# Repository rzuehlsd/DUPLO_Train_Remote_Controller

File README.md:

# DUPLO Train Remote Controller System

**A event-driven train remote control system for LEGO DUPLO, built on ESP32, FreeRTOS, and Bluetooth Low Energy (BLE).**

Copyright (c) 2022-2025 Ralf Zühlsdorff

This project is licensed under the terms of the MIT License. See the License section below for details.

----
## Table of Contents

- [DUPLO Train Remote Controller System](#duplo-train-remote-controller-system)
  - [Table of Contents](#table-of-contents)
  - [Project Overview](#project-overview)
  - [User Interface](#user-interface)
    - [Quick Start: Connecting a DUPLO Train](#quick-start-connecting-a-duplo-train)
    - [Button \& Encoder Actions](#button--encoder-actions)
    - [Optical Feedback (Controller RGB LED)](#optical-feedback-controller-rgb-led)
    - [Implemented Sensor Callbacks](#implemented-sensor-callbacks)
    - [Auto-Sleep \& Wake-Up](#auto-sleep--wake-up)
  - [Architecture Overview](#architecture-overview)
    - [Dual-Core Strategy](#dual-core-strategy)
    - [Future Improvements](#future-improvements)
  - [System Architecture](#system-architecture)
    - [Multi-Task Processing with Bidirectional Communication](#multi-task-processing-with-bidirectional-communication)
    - [Three-Layer Architecture](#three-layer-architecture)
    - [duploHub.init() Bootstrapping Flow](#duplohubinit-bootstrapping-flow)
  - [Features](#features)
  - [Hardware Requirements](#hardware-requirements)
    - [Primary Hardware](#primary-hardware)
    - [Supported LEGO Hardware](#supported-lego-hardware)
    - [Technical Specifications](#technical-specifications)
  - [Hardware Design](#hardware-design)
  - [Software Dependencies](#software-dependencies)
    - [Platform](#platform)
    - [Libraries](#libraries)
    - [Library Versions](#library-versions)
  - [Installation](#installation)
    - [1. Environment Setup](#1-environment-setup)
    - [2. Project Build \& Upload](#2-project-build--upload)
    - [3. Hardware Setup](#3-hardware-setup)
  - [Usage](#usage)
    - [Basic Operation](#basic-operation)
    - [Expected Serial Debug Output](#expected-serial-debug-output)
  - [API Reference](#api-reference)
    - [DuploHub Class](#duplohub-class)
      - [Connection Management](#connection-management)
      - [Control Methods (Thread-Safe)](#control-methods-thread-safe)
      - [Information Methods](#information-methods)
      - [Event Callbacks](#event-callbacks)
    - [DuploHubExtended Class (Sensor Support)](#duplohubextended-class-sensor-support)
      - [Sensor Callbacks](#sensor-callbacks)
      - [Sensor Activation (Thread-Safe)](#sensor-activation-thread-safe)
      - [Example Usage](#example-usage)
    - [Available Colors](#available-colors)
    - [Motor Speed Range](#motor-speed-range)
  - [System Monitoring](#system-monitoring)
    - [Status Information](#status-information)
    - [Log Message Prefixes](#log-message-prefixes)
  - [Troubleshooting](#troubleshooting)
    - [Common Issues \& Solutions](#common-issues--solutions)
      - [Connection Problems](#connection-problems)
      - [Task Failures](#task-failures)
      - [Command Delays](#command-delays)
    - [Debug Mode](#debug-mode)
  - [Development](#development)
    - [Project Structure](#project-structure)
    - [Adding New Features](#adding-new-features)
      - [New Train Commands](#new-train-commands)
      - [New Hub Types](#new-hub-types)
    - [Code Style Guidelines](#code-style-guidelines)
  - [Contributing](#contributing)
    - [Development Process](#development-process)
    - [Testing Checklist](#testing-checklist)
  - [Links](#links)
  - [License](#license)
  - [Acknowledgments](#acknowledgments)

---

## Project Overview

This project implements a robust, multi-layered, event-driven train controller for LEGO DUPLO trains. 

The system not only covers the firmware to controll the DUPLO train but also the required hardware and the OpenSCAD files for the case of the handheld controller.

I used a Tenstar Super Mini ESP32-S3 FH4R2 controller (yes, it is totally overkill for this application) because it provides onboard functionality as a RGB LED (used for user feedback) and a charging controller for a 3.7V Lithium battery. This onboard functionality reduced the required external components for the handheld controller to only 6 SMD switches, a rotary encoder and a few SMD resistors plus 1 capacitor.

The firmware builds on top of the open-source [Legoino](https://github.com/corneliusmunz/legoino) library created by Cornelius Munz, reusing its Powered Up protocol support while adding a hardened hardware abstraction tailored to ESP32 dual-core devices. Using both cores to implement the app signifficantly increased the overall reliability.

Key pillars of the solution include:

- **ESP32 dual-core architecture** (FreeRTOS): BLE communication runs independently from application logic for deterministic responsiveness.
- **Legoino-powered protocol stack**: Proven LEGO Powered Up discovery, device activation, and message parsing.
- **Thread-safe command and sensor queues**: Bidirectional, non-blocking communication between BLE and main application tasks.
- **Automatic connection management**: Self-healing BLE connections with exponential backoff recovery.
- **Enhanced logging and monitoring**: Real-time status, error, and performance reporting.
- **Deep Sleep and Wakeup**: In case no user interactions have been detected for more than 5 minutes the device goes to sleep and can be waked up by pressing the encoder button.

The high-level structure is summarised below; a deeper dive is available in [ARCHITECTURE.md](ARCHITECTURE.md).

## User Interface

THe handheld DUPLO train controller has 6 switches and a rotary encoder to send BLE commands to the DUPLO train hub. User feedback is provided through the onboard RGB LED of the ESP32-S3 controller.

### Quick Start: Connecting a DUPLO Train
- Power on the controller (ESP32) and the DUPLO Train Hub. 
- The DUPLO train will show a **white** blinking front light.
- The RGB LED of the controller turns to **yellow**.
- The controller immediately begins scanning for an active duplo train.
- Once internal initializatioon of the controller is completed the RBB LED turns to **green**. 
- If connected the DUPLO train will show a solid **blue** front light.
- After DUPLO train has connected, the controller’s RGB status LED turns to *blue** and blinks 3 times to confirm link.
- If no hub is found, the status LED pulses **orange** every few seconds to prompt you to power cycle or move the train closer.

### Button & Encoder Actions
- **Rotary encoder (turn):** Proportionally ramps the train motor between full reverse, neutral, and full forward with a tactile centre detent to simplify stops.
- **Rotary encoder (press):** Wakes the controller from deep sleep.
- **Record button:** Starts or stops capture of the current driving session, including speed, light, and sound changes for later replay.
- **Play button:** Replays the most recently recorded session, mirroring the captured timing for motor, LED, and audio cues. Press again to stop replay.
- **Stop button:** Issues an immediate emergency stop, cutting motor power and triggering the associated brake feedback sequence. To start normal operation the stop button **HAS TO BE PRESSED AGAIN**!
- **Light button:** Cycles through the preset DUPLO hub LED colours so the train can be themed without using a screen or app.
- **Sound button:** Steps through the curated horn, brake, and station audio effects for interactive play.
- **Water button:** Runs the refill routine, pausing the train, playing the refill sound, and resuming at the previous throttle setting.

### Optical Feedback (Controller RGB LED)
- **Blue (pulsing 5 times):** Connection to a DUPLO hub establish and ready for commands.
- **Red (slow blinking):** Recording action sequence.
- **Yellow (slow blinking):** Replaying action sequence.
- **Red (steady):** Emergency stop engaged. Goes off if button is engaged again
- **Red (fast pulses 5 times):** Signals low voltage of DUPLO train battery every 300 seconds

### Implemented Sensor Callbacks

The controller provides callback implementations for speed, voltage and color sensor events. While the speed sensor is currently not used, the voltage sensor gives warning feedback, if battery voltage of DUPLO Train drops below 5V.

The color sensor is used to detect the color bricks provided with the DUPLO train set to trigger preprogrammed actions. The detection of the correct colors is very tricky as it depends on the reflection of the color bricks. So expect some wrong colors to be detected. As we overwrite the preprogrammed actions here is a short description of the implemented actions:

- **RED** triggers a stop of the train with brake sound and red headlights
- **YELLOW** triggers departure of the train with yellow blinking headlights and horn sound
- **BLUE** triggers water refill action with blinking blue headlight, stop of train, water refill sound and departure of train with last defined speed

Currently all other colored bricks just set the headlight to the respective color.

### Auto-Sleep & Wake-Up
- After **5 minutes** without button presses or encoder turns, the controller enters deep sleep to save power; the status LED fades out to indicate standby.
- To reactivate, press the rotary encoder once to start initialization and connection cycle again

---
## Architecture Overview

The firmware is organised into three cooperating layers:

1. **Application Layer (`TrainController`)** – orchestrates user input, status LED feedback, replay/record logic, and system health checks.
2. **Hardware Abstraction Layer (`DuploHub`)** – maintains thread-safe command/response queues, sensors, and lifecycle management for the BLE task.
3. **Protocol Layer (`myLegoHub`/Legoino)** – bridges to the LEGO Powered Up protocol, handling device discovery and low-level message encoding.

These layers communicate exclusively through FreeRTOS queues and callbacks, which allows the BLE task and user interface to stay decoupled. The full architectural description, sequence diagrams, and performance considerations are documented in [ARCHITECTURE.md](ARCHITECTURE.md).

### Dual-Core Strategy

The ESP32’s two cores are used deliberately to isolate time-critical communication from user-driven workloads:

- **Core 0** is dedicated to the BLE stack (NimBLE) and the `DuploHub` task, guaranteeing consistent connection upkeep and sensor polling under tight timing constraints.
- **Core 1** runs the Arduino loop (`TrainController`), handling rotary encoder updates, button ladders, response queue processing, and visual/audible feedback without blocking the BLE stack.

This separation keeps latency predictable—even when the UI is busy—and prevents sensor interrupts or sound/LED routines from starving the communication pipeline.

### Future Improvements

- Function to pair with train (store ID and use when connecting)

---
## System Architecture

### Multi-Task Processing with Bidirectional Communication

```mermaid
graph LR
   MainTask["<b>Core 1 – Main Task</b><br/>• Application logic<br/>• User interface<br/>• Status display<br/>• Demo logic<br/>• Sensor processing<br/>• Event callbacks"]

   BleTask["<b>Core 0 – BLE Task</b><br/>• BLE operations<br/>• Hub connection<br/>• Motor commands<br/>• LED control<br/>• Sensor setup<br/>• Data parsing"]

   MainTask --> |CommandQueue| BleTask

   BleTask --> |SensorQueue| MainTask

   classDef queueStyle fill:#f2f2f2,stroke:#333,stroke-width:1px
   class CommandQueue,SensorQueue queueStyle
```

### Three-Layer Architecture

```mermaid
graph LR
   Layer1["<b>Layer 1: Application Layer</b><br/>• Train demo sequence &amp; state management<br/>• User interface &amp; status monitoring<br/>• High-level control logic<br/>• Connection event handling<br/>• Sensor data processing &amp; callbacks"]

   Layer2["<b>Layer 2: Hardware Abstraction</b><br/>• Thread-safe command queue<br/>• Bidirectional FreeRTOS queues<br/>• Multi-task management (dual-core ESP32)<br/>• Connection state management<br/>• Automatic recovery &amp; error handling<br/>• Sensor routing &amp; callback management"]

   Layer3["<b>Layer 3: Protocol Layer</b><br/>• LEGO Powered Up protocol<br/>• Bluetooth LE communication<br/>• Device discovery &amp; connection<br/>• Motor &amp; LED control commands<br/>• Sensor data parsing &amp; callbacks"]

   Layer1 -->|Clean API + sensor callbacks| Layer2
   Layer2 -->|Protocol interface + sensor integration| Layer3
```

### duploHub.init() Bootstrapping Flow

The following sequence diagram visualizes how the application brings up the BLE infrastructure when `duploHub.init()` is called from `TrainController::setup()`.

```mermaid
sequenceDiagram
   participant TC as TrainController::setup
   participant DH as DuploHub
   participant RTOS as FreeRTOS Scheduler
   participant BLE as BLE Task (Core 0)
   participant Lpf2 as Lpf2Hub

   TC->>DH: init()
   activate DH
   DH->>DH: initFreeRTOS()
   DH->>RTOS: xTaskCreatePinnedToCore(bleTaskWrapper)
   RTOS-->>DH: Task handle
   deactivate DH
   DH-->>TC: return

   RTOS->>BLE: schedule bleTaskWrapper(this)
   activate BLE
   BLE->>DH: bleTaskFunction()
   loop continuous loop
      BLE->>DH: updateBLE()
      alt Hub disconnected
         DH->>Lpf2: hub.init()
      else Hub connecting
         DH->>Lpf2: connectHub()
      end
      opt Connection state change
         DH-->>TC: onConnectedCallback()/onDisconnectedCallback()
      end
      BLE->>DH: processCommandQueue()
      DH->>Lpf2: Execute queued command
      BLE->>BLE: vTaskDelay(50 ms)
   end
```

---

## Features

- **Multi-Task BLE Management**: BLE operations run on a dedicated core, never blocking the main application.
- **Automatic Connection & Recovery**: Discovers, connects, and reconnects to DUPLO train hubs automatically.
- **Thread-Safe Commands**: Queue-based command system prevents race conditions.
- **Real-Time Control**: Low-latency motor speed and LED color control driven by rotary encoder input.
- **Sensor Integration**: Color, speed, and voltage sensors with callback support and queue isolation.
- **Color Stability Filtering**: Timer-based debounce suppresses transient color readings before they reach the UI.
- **Command Recording & Replay**: Capture user sessions and play them back with preserved timing.
- **Professional Logging**: Detailed, component-specific log messages and system status monitoring.
- **Idle Power Management**: Automatic deep sleep after configurable idle periods, resume via encoder button.
- **Resource Management**: Proper FreeRTOS object lifecycle management.
- **Input Abstraction**: ADC button ladder and rotary encoder handlers with debounced callbacks.
- **Demo Mode**: Non-blocking demo sequence with visual feedback and safety features.

---

## Hardware Requirements

### Primary Hardware

- **ESP32 Development Board ESP32-S3 Super Mini** (see link below)
    I use the Tenstar ESP32-S3 FH4R2 SuperMini which also includes cuircits to charge a 3.7V Lithium battery.
- **LEGO DUPLO Train Hub** with motor connected to Port A
- **USB Type C Cable** for programming and power

### Supported LEGO Hardware

- DUPLO Train Hub (Hub Type: `DUPLO_TRAIN_HUB`)
- DUPLO Train Motors (connected to Port A)
- Compatible with other Powered Up hubs (with minor modifications)

### Technical Specifications

- **Microcontroller**: ESP32 (dual-core, 240MHz)
- **Memory**: 520KB SRAM, 4MB Flash minimum
- **Connectivity**: Bluetooth 4.2 LE
- **Operating Voltage**: 3.3V
- **Power Consumption**: ~130mA during active BLE operation

---

## Hardware Design

The following images show the KiCAD 3d view of the controller pcb and the OpenSCAD view of the controller case. To design the controller case the MachineBlocks library from pks5 (https://github.com/pks5/machineblocks) has been used.

- A dedicated ESP32-S3 carrier board with battery management and button/encoder headers is captured in KiCad inside `hardware/DuploTrainController NG`.
- A matching printable enclosure is modelled in OpenSCAD in `hardware/Case`, which also embeds the MachineBlocks library to speed up iteration on DUPLO-sized parts.

See [hardware/Hardware.md](hardware/Hardware.md) for a detailed description of the custom controller hardware.

## Software Dependencies

### Platform
- **PlatformIO**: Development platform
- **ESP32 Arduino Framework**: Core ESP32 support
- **FreeRTOS**: Real-time operating system (included with ESP32)

### Libraries

- **Legoino**: LEGO Powered Up protocol implementation by Cornelius Munz
- **NimBLE-Arduino**: Bluetooth Low Energy stack

All other libs used are provided as source in include and src dir.

### Library Versions

```ini
[env:esp32dev]
platform = espressif32
board = esp32dev
framework = arduino
lib_deps = 
    legoino/Legoino
    h2zero/NimBLE-Arduino
```

---

## Installation

Th development of this code has been done with MS Studio Code and PlatformIO.

### 1. Environment Setup

```bash
# Install PlatformIO CLI
pip install platformio

# Clone the repository
git clone <repository-url>
cd DuploTrain
```

### 2. Project Build & Upload

```bash
# Build the project
pio run

# Upload to ESP32
pio run --target upload

# Open serial monitor
pio device monitor
```

### 3. Hardware Setup

1. Connect ESP32 to computer via USB
2. Power on your DUPLO train hub
3. Ensure motor is connected to Port A of the hub
4. Upload and run the code

---

## Usage

### Basic Operation

1. **Startup**: System automatically starts and begins scanning for DUPLO hubs
2. **Connection**: When hub is found, automatic connection is established
3. **Demo**: Once connected, the demo sequence begins automatically
4. **Monitoring**: Status information is displayed every 10 seconds

### Expected Serial Debug Output

```text
TrainController: Starting up...
DuploHub: FreeRTOS objects initialized
DuploHub: BLE task started successfully
TrainController: Ready - BLE task running, waiting for hub connection...
BLE Task: Started successfully
BLE Task: Attempting initial connection to hub...
BLE Task: Connected to HUB
TrainController: Hub connected - initializing train demo!
TrainController: Starting train demo sequence...
TrainController Status - BLE Task: Running, Hub Connected: Yes, Demo Active: Yes
```

---

## API Reference

### DuploHub Class

#### Connection Management

```cpp
void startBLETask();                    // Start background BLE task
void stopBLETask();                     // Stop background BLE task
bool isConnected();                     // Check connection status (thread-safe)
bool isConnecting();                    // Check if connecting (thread-safe)
bool isDisconnected();                  // Check if disconnected (thread-safe)
bool isBLETaskRunning();                // Check BLE task status
```

#### Control Methods (Thread-Safe)

```cpp
void setMotorSpeed(int speed);          // Set motor speed (-100 to 100)
void stopMotor();                       // Stop motor immediately
void setLedColor(Color color);          // Set hub LED color
void setHubName(const char* name);      // Set hub name
```

#### Information Methods

```cpp
std::string getHubAddress();            // Get hub BLE address
std::string getHubName();               // Get hub name
byte getMotorPort();                    // Get configured motor port
void setMotorPort(byte port);           // Set motor port
```

#### Event Callbacks

```cpp
void setOnConnectedCallback(ConnectionCallback callback);     // Hub connected event
void setOnDisconnectedCallback(ConnectionCallback callback);  // Hub disconnected event
```

### DuploHubExtended Class (Sensor Support)

#### Sensor Callbacks

```cpp
typedef void (*ColorSensorCallback)(int color, byte port);
typedef void (*DistanceSensorCallback)(int distance, byte port);
typedef void (*ButtonCallback)(ButtonState state);

void setOnColorSensorCallback(ColorSensorCallback callback);      // Color sensor events
void setOnDistanceSensorCallback(DistanceSensorCallback callback);  // Distance sensor events
void setOnButtonCallback(ButtonCallback callback);                 // Button press events
```

#### Sensor Activation (Thread-Safe)

```cpp
void activateColorSensor(byte port);      // Activate color sensor on specified port
void activateDistanceSensor(byte port);   // Activate distance sensor on specified port
void activateButton();                    // Activate hub button monitoring
```

#### Example Usage

```cpp
// Color-based speed control
void onColorDetected(int color, byte port) {
    if (color == (byte)Color::RED) {
        duploHub.stopMotor();           // Emergency stop
    } else if (color == (byte)Color::GREEN) {
        duploHub.setMotorSpeed(50);     // Fast speed
    }
    duploHub.setLedColor((Color)color); // Match LED to detected color
}

// Setup
DuploHubExtended duploHub;
duploHub.setOnColorSensorCallback(onColorDetected);
duploHub.activateColorSensor((byte)PoweredUpHubPort::B);
```

### Available Colors

```cpp
BLACK, PINK, PURPLE, BLUE, LIGHTBLUE, CYAN, GREEN, YELLOW, ORANGE, RED, WHITE
```

### Motor Speed Range

- **Range**: -100 to 100
- **Positive**: Forward direction
- **Negative**: Backward direction
- **Zero**: Stop (equivalent to `stopMotor()`)

---

## System Monitoring

- **BLE Task**: Runs on Core 0, Priority 2
- **Main Loop**: Runs on Core 1, Priority 1
- **Connection Checks**: Every 1 second
- **Command Processing**: Every 50ms
- **Status Updates**: Every 10 seconds

### Status Information

The system provides comprehensive monitoring through serial output:

```text
TrainController Status - BLE Task: Running, Hub Connected: Yes, Demo Active: Yes
```

### Log Message Prefixes

- **`TrainController:`** - Main application messages
- **`BLE Task:`** - Background BLE task messages  
- **`DuploHub:`** - Hardware abstraction layer messages
- **`ERROR:`** - Critical system errors
- **`WARNING:`** - Non-critical issues

---

## Troubleshooting

### Common Issues & Solutions

#### Connection Problems
- Ensure DUPLO hub is powered on and in pairing mode
- Check if hub is already connected to another device
- Reset hub by holding button for 10 seconds
- Move ESP32 closer to hub (within 5 meters)

#### Task Failures
- Check available heap memory: `ESP.getFreeHeap()`
- Reduce other running tasks
- Increase stack size in `startBLETask()`

#### Command Delays
- Check command queue status
- Verify BLE connection stability
- Reduce command frequency in application

### Debug Mode

Enable detailed debugging by adding to `platformio.ini`:

```ini
build_flags = -DCORE_DEBUG_LEVEL=4
monitor_filters = esp32_exception_decoder
```

---

## Development

### Project Structure

```text
DuploTrain NG/
├── hardware/
│   ├── Case/
│   │   ├── Controller.scad
│   │   ├── MachineBlocks/
│   │   └── lib/
│   ├── DuploTrainController NG/
│   │   ├── DuploTrainController NG.kicad_pcb
│   │   ├── DuploTrainController NG.kicad_sch
│   │   ├── DuploTrainController NG.kicad_pro
│   │   ├── DuploTrainController NG.kicad_prl
│   │   ├── DuploTrainController NG.kicad_pcb.zip
│   │   ├── 5 Buttons an ADC.xlsx
│   │   └── Gerber/
│   └── README.md
├── include/
│   ├── ADCButton.h
│   ├── DuploHub.h
│   ├── StatusLED.h
│   ├── SystemMemory.h
│   ├── debug.h
│   └── myLegoHub.h
├── lib/
│   ├── Legoino/
│   └── NimBLE-Arduino/
├── src/
│   ├── ADCButton.cpp
│   ├── DuploHub.cpp
│   ├── StatusLED.cpp
│   ├── SytemMemory.cpp
│   ├── TrainController.cpp
│   ├── debug.cpp
│   └── myLegoHub.cpp
├── test/
│   ├── DuploTrainTests.cpp
│   ├── DuploTrainTests.h
│   └── README.md
├── ARCHITECTURE.md
├── CHANGELOG.md
├── platformio.ini
└── README.md
```

### Adding New Features

#### New Train Commands
1. Add command type to `CommandType` enum in `DuploHub.h`
2. Add command data structure to `HubCommand` union
3. Implement thread-safe method in `DuploHub` class
4. Add processing logic to `processCommandQueue()`

#### New Hub Types
1. Modify hub type detection in BLE scanning
2. Add hub-specific command handling
3. Update motor port configurations if needed

### Code Style Guidelines
- Use clear, descriptive variable names
- Add comprehensive comments for complex logic
- Follow Arduino coding standards
- Use thread-safe practices for shared data
- Include error handling for all operations

---

## Contributing

### Development Process
1. Fork the repository
2. Create feature branch (`git checkout -b feature/new-feature`)
3. Follow code style guidelines
4. Add comprehensive comments
5. Test thoroughly on hardware
6. Submit pull request with detailed description

### Testing Checklist
- [ ] Builds without warnings
- [ ] Connects to DUPLO hub successfully
- [ ] Motor control works in both directions
- [ ] LED colors change correctly
- [ ] Reconnection works after power cycle
- [ ] No memory leaks during long operation
- [ ] Task monitoring shows healthy system

---

## Links

- [ESP32 Super Mini](https://de.aliexpress.com/item/1005010463397231.html?spm=a2g0o.productlist.main.4.54df76f7WPz7SU&aem_p4p_detail=202512080110153593710143562560003446235&algo_pvid=2100b7c8-e2b1-442a-bd2c-1100bbdba2ac&algo_exp_id=2100b7c8-e2b1-442a-bd2c-1100bbdba2ac-3&pdp_ext_f=%7B%22order%22%3A%222%22%2C%22eval%22%3A%221%22%2C%22fromPage%22%3A%22search%22%7D&pdp_npi=6%40dis%21EUR%215.49%215.49%21%21%2144.13%2144.13%21%40211b612817651850154035955e1646%2112000052495017919%21sea%21DE%216288981052%21X%211%210%21n_tag%3A-29919%3Bd%3A6804e1a2%3Bm03_new_user%3A-29895&curPageLogUid=KEHYNdqLToXo&utparam-url=scene%3Asearch%7Cquery_from%3A%7Cx_object_id%3A1005010463397231%7C_p_origin_prod%3A&search_p4p_id=202512080110153593710143562560003446235_1)
- [Lithium Battery 3.7V](https://de.aliexpress.com/item/1005004378108918.html?spm=a2g0o.detail.pcDetailTopMoreOtherSeller.5.39c7kCFakCFaZ4&gps-id=pcDetailTopMoreOtherSeller&scm=1007.14452.478275.0&scm_id=1007.14452.478275.0&scm-url=1007.14452.478275.0&pvid=03756532-275c-4ab9-bd8a-2053af674cb4&_t=gps-id:pcDetailTopMoreOtherSeller,scm-url:1007.14452.478275.0,pvid:03756532-275c-4ab9-bd8a-2053af674cb4,tpp_buckets:668%232846%238108%231977&pdp_ext_f=%7B%22order%22%3A%2247%22%2C%22eval%22%3A%221%22%2C%22sceneId%22%3A%2230050%22%2C%22fromPage%22%3A%22recommend%22%7D&pdp_npi=6%40dis%21EUR%215.68%214.09%21%21%216.46%214.65%21%4021038e6617651853991155852e878e%2112000028967861661%21rec%21DE%216288981052%21X%211%210%21n_tag%3A-29919%3Bd%3A6804e1a2%3Bm03_new_user%3A-29895&utparam-url=scene%3ApcDetailTopMoreOtherSeller%7Cquery_from%3A%7Cx_object_id%3A1005004378108918%7C_p_origin_prod%3A&search_p4p_id=202512080116391515856091447492685637_4)
- [MachineBlocks](https://github.com/pks5/machineblocks)
---

## License

MIT License

Permission is hereby granted, free of charge, to any person obtaining a copy
of this software and associated documentation files (the "Software"), to deal
in the Software without restriction, including without limitation the rights
to use, copy, modify, merge, publish, distribute, sublicense, and/or sell
copies of the Software, and to permit persons to whom the Software is
furnished to do so, subject to the following conditions:

The above copyright notice and this permission notice shall be included in all
copies or substantial portions of the Software.

THE SOFTWARE IS PROVIDED "AS IS", WITHOUT WARRANTY OF ANY KIND, EXPRESS OR
IMPLIED, INCLUDING BUT NOT LIMITED TO THE WARRANTIES OF MERCHANTABILITY,
FITNESS FOR A PARTICULAR PURPOSE AND NONINFRINGEMENT. IN NO EVENT SHALL THE
AUTHORS OR COPYRIGHT HOLDERS BE LIABLE FOR ANY CLAIM, DAMAGES OR OTHER
LIABILITY, WHETHER IN AN ACTION OF CONTRACT, TORT OR OTHERWISE, ARISING FROM,
OUT OF OR IN CONNECTION WITH THE SOFTWARE OR THE USE OR OTHER DEALINGS IN THE
SOFTWARE.

---

## Acknowledgments

- **Cornelius Munz** - Legoino library creator
- **LEGO Group** - DUPLO and Powered Up hardware
- **Espressif** - ESP32 platform
- **Arduino Community** - Framework and libraries

---

**Version:** 2.0.0  
**Last Updated:** July 2025  
**Compatibility:** ESP32, Arduino Framework, PlatformIO

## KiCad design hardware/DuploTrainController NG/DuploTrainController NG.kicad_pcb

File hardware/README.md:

# Hardware Assets

This directory now contains the complete KiCad design files for the **DuploTrainController NG** handheld controller together with the generated Gerber fabrication outputs.  The top-level structure is:

```
hardware/
├── Case/                       # Enclosure or mechanical assets (empty placeholder for now)
├── DuploTrainController NG/    # KiCad project directory
│   ├── DuploTrainController NG.kicad_pro
│   ├── DuploTrainController NG.kicad_pcb
│   ├── DuploTrainController NG.kicad_sch
│   ├── DuploTrainController NG.kicad_prl
│   ├── DuploTrainController NG.kicad_pcb.zip
│   ├── 5 Buttons an ADC.xlsx
│   ├── Gerber/                 # Fabrication outputs
│   └── fp-info-cache           # Footprint cache
└── README.md                   # This document
```

Open the project in KiCad using `DuploTrainController NG.kicad_pro`.  The spreadsheet documents the ADC ladder calculations for the push buttons.  The `Gerber/` folder contains ready-to-send manufacturing files that match the current PCB revision.

> **Note:** Large binary and generated files are intentionally stored in version control so collaborators have an exact copy of the board as fabricated.  If you regenerate outputs, please audit the diffs before committing to avoid unnecessary churn.

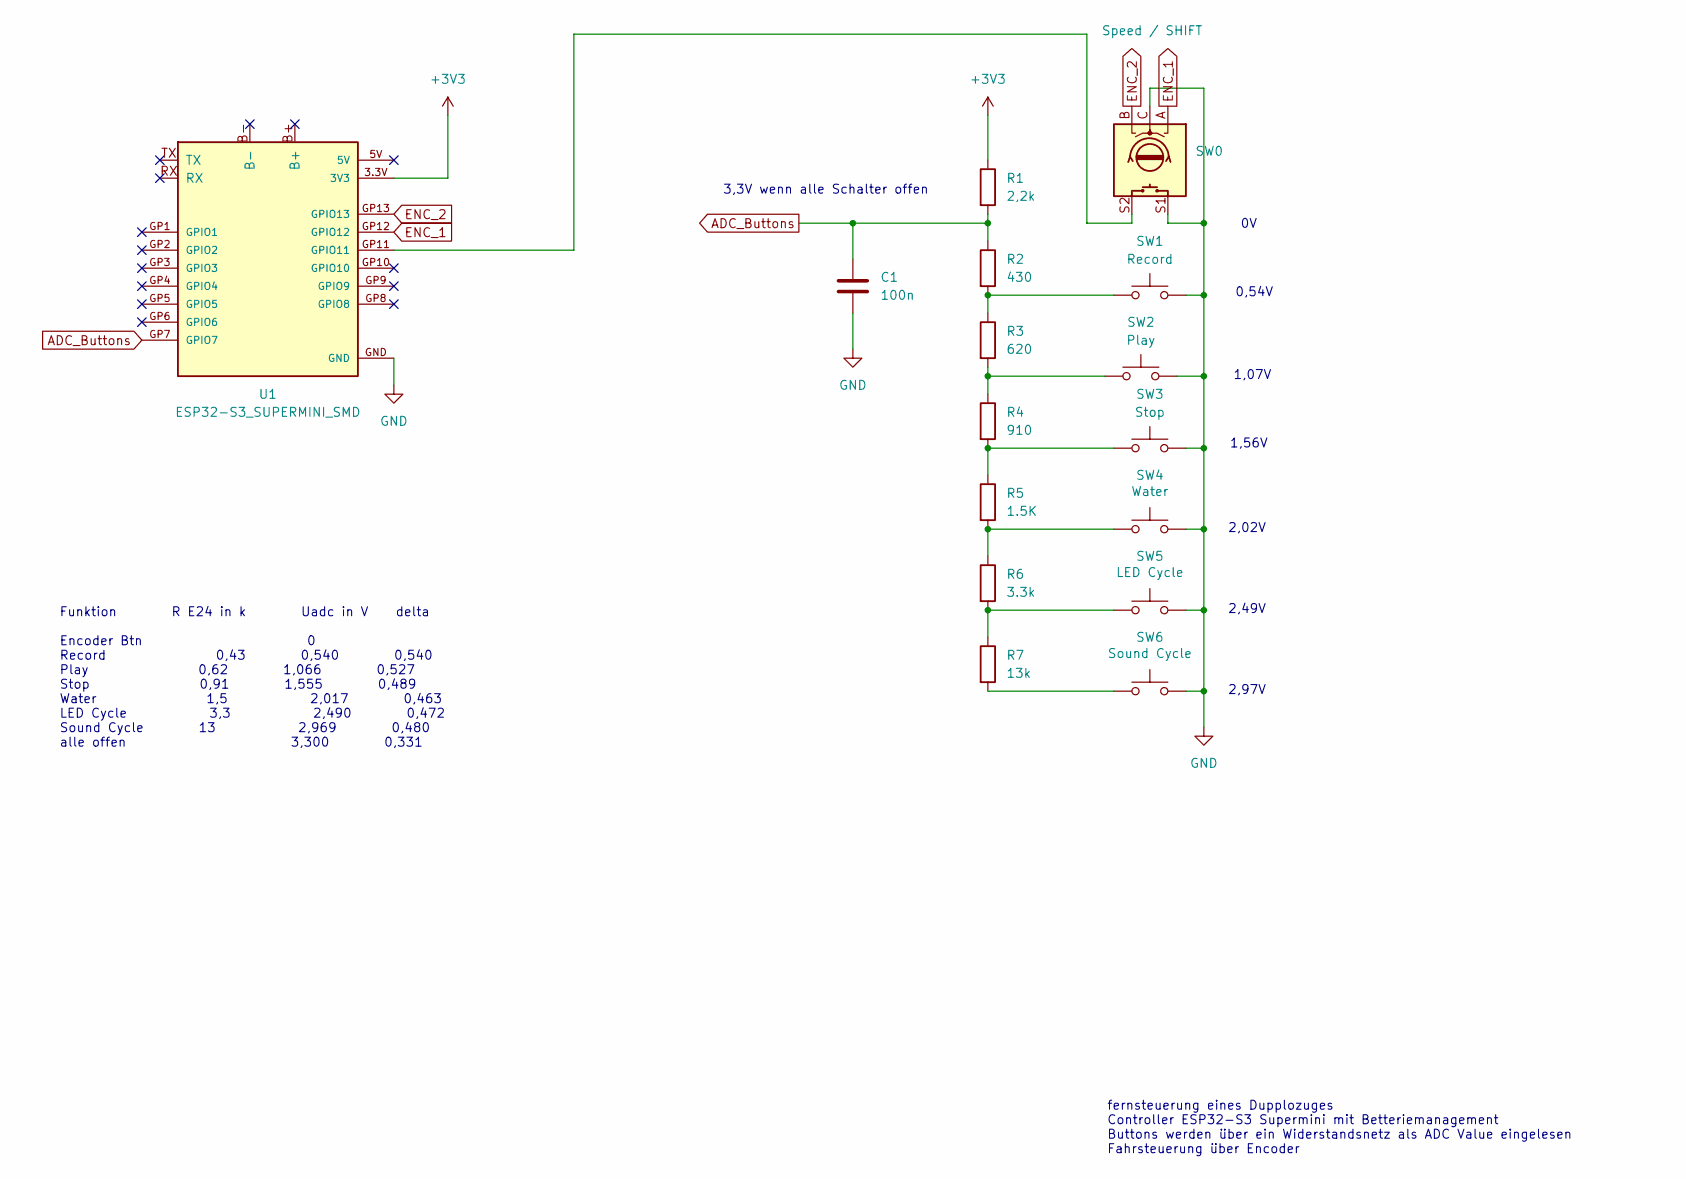
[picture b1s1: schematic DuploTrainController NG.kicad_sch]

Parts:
C1: 100n; C_Rect_L7.0mm_W2.0mm_P5.00mm
R1: 2,2k; R_0805_2012Metric_Pad1.20x1.40mm_HandSolder
R2: 430; R_0805_2012Metric_Pad1.20x1.40mm_HandSolder
R3: 620; R_0805_2012Metric_Pad1.20x1.40mm_HandSolder
R4: 910; R_0805_2012Metric_Pad1.20x1.40mm_HandSolder
R5: 1.5K; R_0805_2012Metric_Pad1.20x1.40mm_HandSolder
R6: 3.3k; R_0805_2012Metric_Pad1.20x1.40mm_HandSolder
R7: 13k; R_0805_2012Metric_Pad1.20x1.40mm_HandSolder
SW0: Speed / SHIFT; RotaryEncoder_Bourns_Vertical_PEC12R-3x17F-Sxxxx
SW1: Record; SW_SPST_Omron_B3FS-101xP
SW2: Play; SW_SPST_Omron_B3FS-101xP
SW3: Stop; SW_SPST_Omron_B3FS-101xP
SW4: Water; SW_SPST_Omron_B3FS-101xP
SW5: LED Cycle; SW_SPST_Omron_B3FS-101xP
SW6: Sound Cycle; SW_SPST_Omron_B3FS-101xP
U1: ESP32-S3_SUPERMINI_SMD; MODULE_ESP32-S3_SUPERMINI_SMD

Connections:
+3V3: R1.1, U1.3.3V (3V3)
ADC_Buttons: C1.1, R1.2, R2.1, U1.GP7 (GPIO7)
ENC_1: SW0.A, U1.GP12 (GPIO12)
ENC_2: SW0.B, U1.GP13 (GPIO13)
GND: C1.2, SW0.C, SW0.S1, SW1.2, SW2.2, SW3.2, SW4.2, SW5.2, SW6.2, U1.GND
unnamed: R2.2, R3.1, SW1.1
unnamed: R3.2, R4.1, SW2.1
unnamed: R4.2, R5.1, SW3.1
unnamed: R5.2, R6.1, SW4.1
unnamed: R6.2, R7.1, SW5.1
unnamed: R7.2, SW6.1
unnamed: SW0.S2, U1.GP11 (GPIO11)

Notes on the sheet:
2,02V
0,54V
2,49V
1,07V
fernsteuerung eines Dupplozuges Controller ESP32-S3 Supermini mit Betteriemanagement Buttons werden über ein Widerstandsnetz als ADC Value eingelesen Fahrsteuerung über Encoder
3,3V wenn alle Schalter offen
2,97V
Funktion R E24 in k Uadc in V delta Encoder Btn 0 Record 0,43 0,540 0,540 Play 0,62 1,066 0,527 Stop 0,91 1,555 0,489 Water 1,5 2,017 0,463 LED Cycle 3,3 2,490 0,472 Sound Cycle 13 2,969 0,480 alle offen 3,300 0,331
1,56V

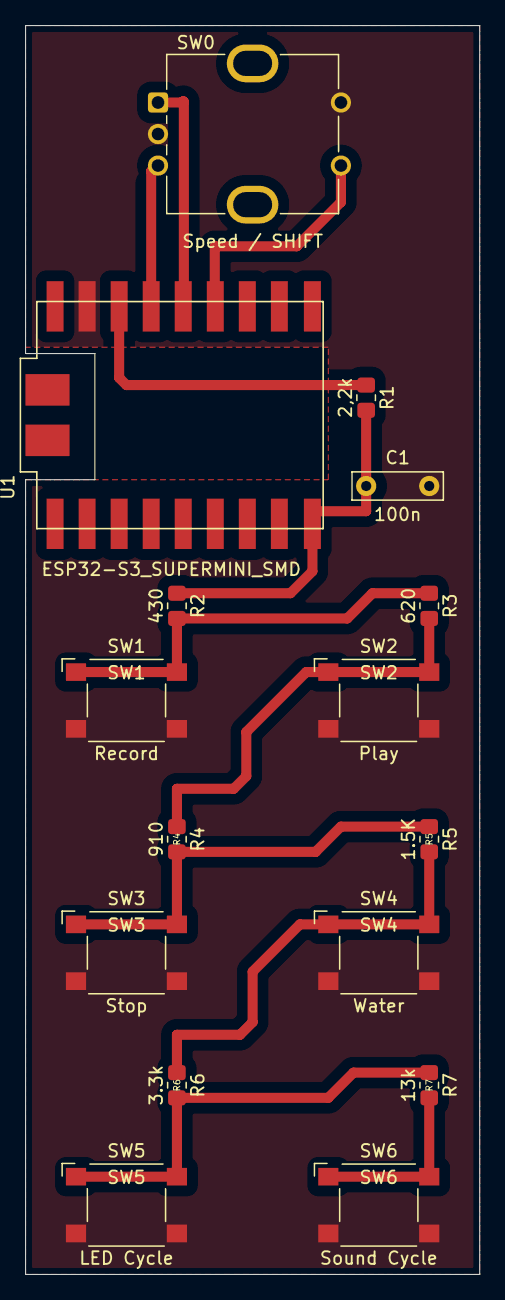
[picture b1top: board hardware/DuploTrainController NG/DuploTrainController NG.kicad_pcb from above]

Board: 2 copper layers, 36.0 x 99.0 mm, 16 parts (0 on the bottom side), 12 nets.

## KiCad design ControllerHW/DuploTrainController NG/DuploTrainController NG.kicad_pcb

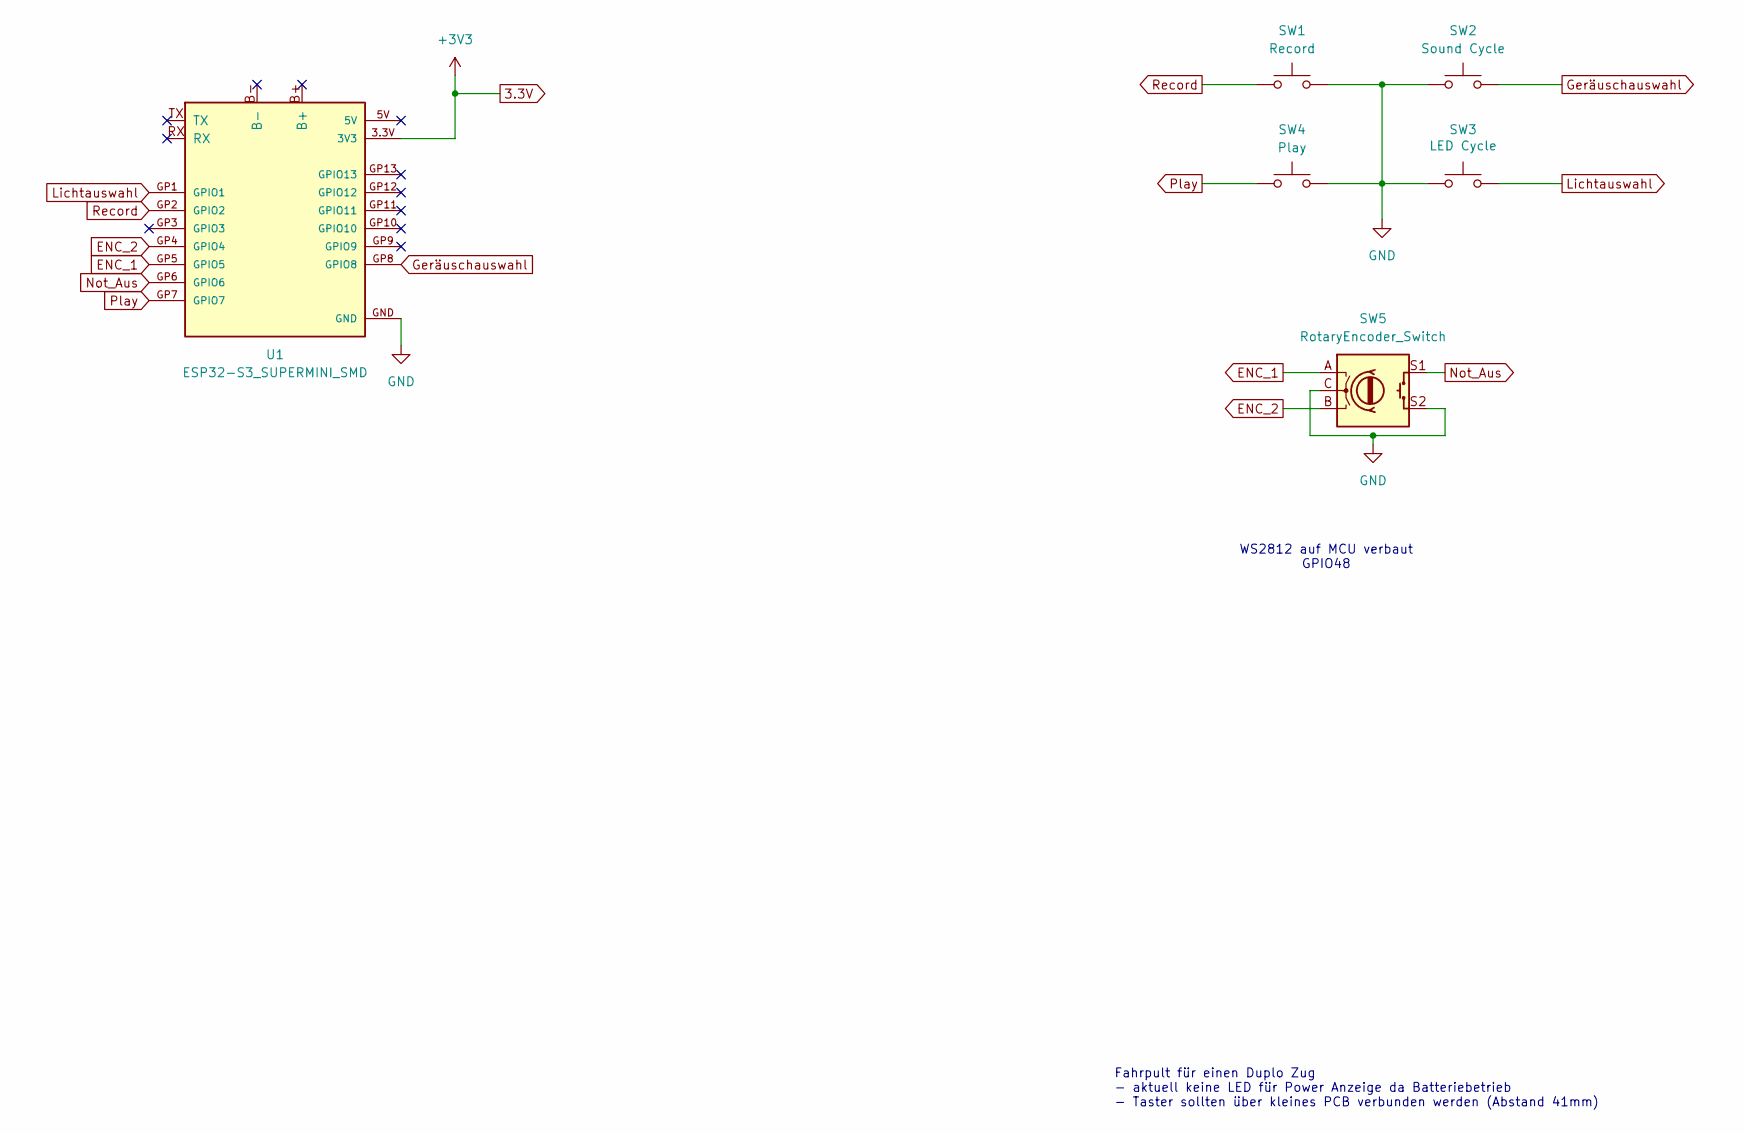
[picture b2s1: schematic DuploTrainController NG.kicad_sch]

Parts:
SW1: Record; SW_Push_1P1T_NO_CK_KSC6xxJ
SW2: Sound Cycle; SW_Push_1P1T_NO_CK_KSC6xxJ
SW3: LED Cycle; SW_Push_1P1T_NO_CK_KSC6xxJ
SW4: Play; SW_Push_1P1T_NO_CK_KSC6xxJ
SW5: RotaryEncoder_Switch; RotaryEncoder_Bourns_Vertical_PEC12R-3x17F-Sxxxx
U1: ESP32-S3_SUPERMINI_SMD; MODULE_ESP32-S3_SUPERMINI_SMD

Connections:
3.3V: U1.3.3V (3V3)
ENC_1: SW5.A, U1.GP5 (GPIO5)
ENC_2: SW5.B, U1.GP4 (GPIO4)
GND: SW1.2, SW2.1, SW3.1, SW4.2, SW5.C, SW5.S2, U1.GND
Geräuschauswahl: SW2.2, U1.GP8 (GPIO8)
Lichtauswahl: SW3.2, U1.GP1 (GPIO1)
Not_Aus: SW5.S1, U1.GP6 (GPIO6)
Play: SW4.1, U1.GP7 (GPIO7)
Record: SW1.1, U1.GP2 (GPIO2)

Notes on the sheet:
Fahrpult für einen Duplo Zug - aktuell keine LED für Power Anzeige da Batteriebetrieb - Taster sollten über kleines PCB verbunden werden (Abstand 41mm)
WS2812 auf MCU verbaut GPIO48

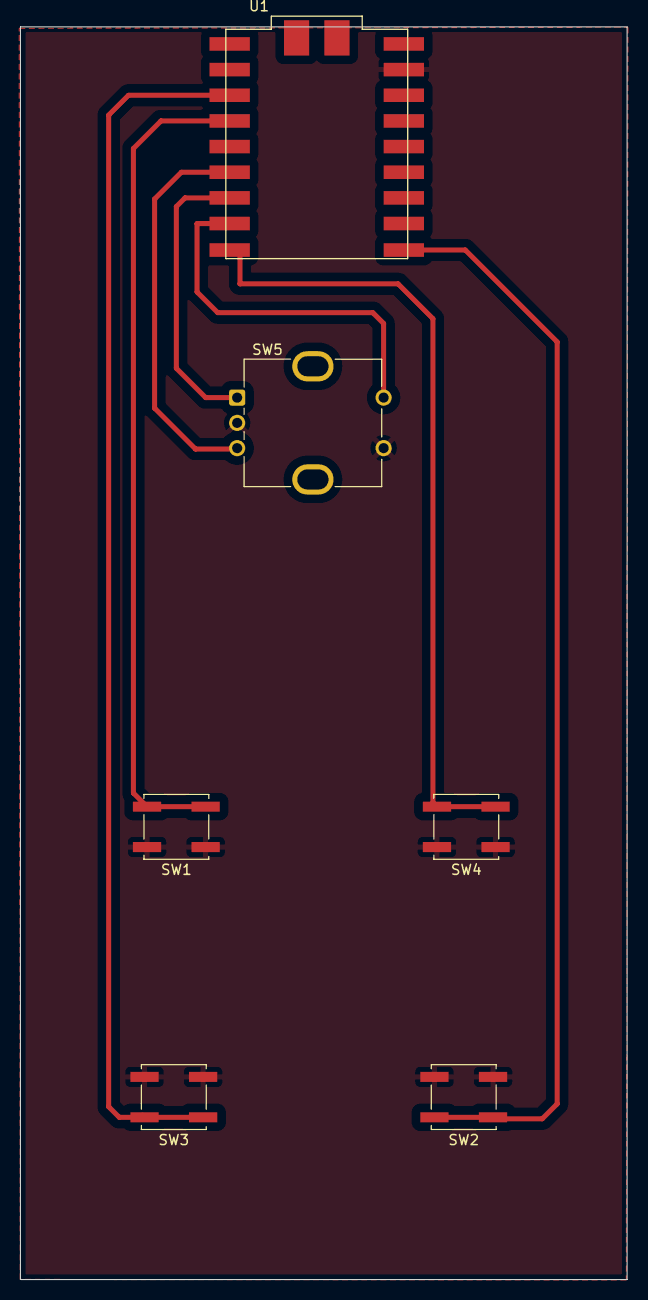
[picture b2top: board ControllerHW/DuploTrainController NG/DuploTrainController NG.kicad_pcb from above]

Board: 2 copper layers, 60.0 x 124.0 mm, 6 parts (0 on the bottom side), 8 nets.

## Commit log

2025-07-20 Initial
2025-07-20 reconnect integrated
2025-07-20 feat: Implement multi-core architecture for DUPLO Train Controller
    - Add DuploHub class with thread-safe API and FreeRTOS integration
    - Implement BLE operations on dedicated task (Core 0)
    - Add command queue system for inter-task communication
    - Rename TrainHub.cpp to TrainController.cpp for semantic clarity
    - Add automatic connection recovery with background monitoring
    - Implement mutex-based synchronization for thread safety
2025-07-20 feat: Add extended sensor support with bidirectional data processing
    - Implement DuploHubExtended class with sensor callback system
    - Add bidirectional FreeRTOS queues (commands + sensor data)
    - Create static callback wrappers for Lpf2Hub integration
    - Add TrainController_Extended.cpp with color-based speed control
    - Implement real-time sensor processing with ~75ms total latency
    - Add comprehensive sensor processing chain documentation
2025-07-21 test shell and documentation
2025-07-21 intermediate state not aligned between cpp and h files
2025-07-21 DuploHub and TrainController implemented with motor controll, color led control and sound control and succesfully implemented Fronend running on core 1 and BLE related backend task running on Core 0 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
2025-07-21 documentation updated High delay between initalization of command and execution in lego device needs further investigation
2025-07-22 playSoung function in Lpf2Hub needs an initialization per call which delays abaout 5 - 10 seconds Investigate further
2025-07-22 Timing results: - setSpedd about 5ms - setColor about 12ms
2025-07-22 testing play sound delay: - delay 5ms
2025-07-24 initiale Implementierung sensor Callback und response queue Test steht noch aus
2025-07-24 - debug log macros und functions generated - mutex print does not allways function - detection of colors with duplo base sensor seems to function, but has to be tested with different duplo color stic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
2025-07-27 intermediate version mit color und speed sensor fehler: kommandos werden nicht übertragen an device
2025-07-27 Sound, LED, Motor, Speed und Color callback ok Speed cb liefert Werte zwischen -255 und + 255, muss ggf in DuploHub angeüpasst werden auf Wertebereich der Motor Speed von -100 bis +100 Color Callback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
2025-07-27 Voltage callback ok, thresholds macros für speed und voltage callback execution eingeführt. Reconnect nach power cycle des Duplo Zuges funktioniert Nächste Schritte: Anbindung an das UI und Test mit 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
2025-07-29 Refactoring: - all test functions have been removed frome TrainController with exception of simple test for motor, sound and led - all not required calls to DuploHub have been removed - unnessesary c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
2025-07-30 Traincontroller Buttons are working after Logging was modified to log without semaphor
2025-07-30 Finale Version (Bis zum ersten Fehler): - alle Funktionstasten ok - Nothalt Taste schaltet den Motor aus und beim 2. TAstendruck läuft der Motor mit alter Richtung und Geschwindigkeit - Fahrregler ka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
2025-07-30 Extended documentation of header files
2025-07-30 extended documentation of cpp files
2025-07-30 duplicated #ifndefs deleted Compiles now without error
2025-07-30 Readme und Architekturbeschreibung überarbeitet
2025-07-30 intermediate version of readme completed
2025-07-30 removed files not needed
2025-07-31 added list of future enhancements to Readme
2025-08-01 small changes
2025-08-01 leanup
2025-08-04 ADC Button Handler funktioniert mit den gesetzten Defaults
2025-08-05 Alle buttonfunktionen ok Record / Replay funktioniert gut, hier ggf. mal die Zeitabstände überprüfen eineg Klasse zur Ansteuerung der RGB LED erstmal nur für eine LED kann noch optimiert werden GAnze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
2025-08-05 still timing issues when replaying
2025-08-12 To Do Liste geschrieben
2025-08-17 Replay wird nur noch einmal ausgeführt
2025-08-17 Blockiern aller Kommandos außer Stop und Replay (zum Beenden des Replay Modus) funktioniert. Stop und Replay beenden sofort das Replay.
2025-08-17 blockierung der Color Sensor Aktionen im Replay Modus ist implementiert. Im Recoord modus werden die durch den Color Sensor identifizierten Aktionen aufgezeichent
2025-08-17 Timing wurde nicht exakt überprüft, scheint aber soweit ok zu sein.
2025-08-17 Status LED funktioniert wie festgelegt bis auf Reaktion auf niedrigen Batterie Level
2025-08-17 Voltage Sensor und Batteriewarnung funktioniert. Alle Statusänderungen werden über LED richtig angezeigt
2025-08-17 Für produktiven Einsatz muss DEBUG ausgeschaltet sein, da sonst die MCU ständig rebootet
2025-08-22 train did not stop on emergency halt
2025-12-05 ZUsätzliche Buttons und Encoder Button funtionieren. Speed handling angepasst und Speed callback aktiviert Probleme bei - ColorCB liefert keine stabilen Werte - init mit Hub Mac Adresse funktioniert 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
2025-12-07 Connect mit vorgegebener Mac Address funktioniert
2025-12-07 Debeouncing of Color Sensor is now ok, but didi not always detect all colors (e.g. blue is detected as green, green is detected correct) Meeds to be check in detail how the mapping with the real Dupl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
2025-12-07 ESP deep sleep and wake up working. Controller goes to sleep after 5 minutes of in activity after first connect. Wakeup with encoder button press. Duplo train connects again and registers all sensor 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
2025-12-07 Corrected a small problem as the system restarted immediatly after going to sleep due to the fact that in sleep mode the encoder button pin was not held high. CAll to rtc_gpio_pullup_en () kept the e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
    Updated documentation in readme and architecture document.
2025-12-07 Added board design as KiCAD files in hardware directory
2025-12-07 small changes to docs
2025-12-08 Update of Documentation
2025-12-08 changes to readme
2025-12-08 Corrected project structure
2025-12-08 small changes to documents
2025-12-09 Added SCAD files for case and updated documentation
2025-12-09 Add enclosure assets and update docs
2025-12-09 added copyright and license
2025-12-09 Update Hardware.md with author and license detailscopyright
    Added author, copyright, and license information to Hardware.md
2025-12-09 Add all hardware/DuploTrainController NG files as regular files, remove submodule link
2025-12-09 updated doc files
